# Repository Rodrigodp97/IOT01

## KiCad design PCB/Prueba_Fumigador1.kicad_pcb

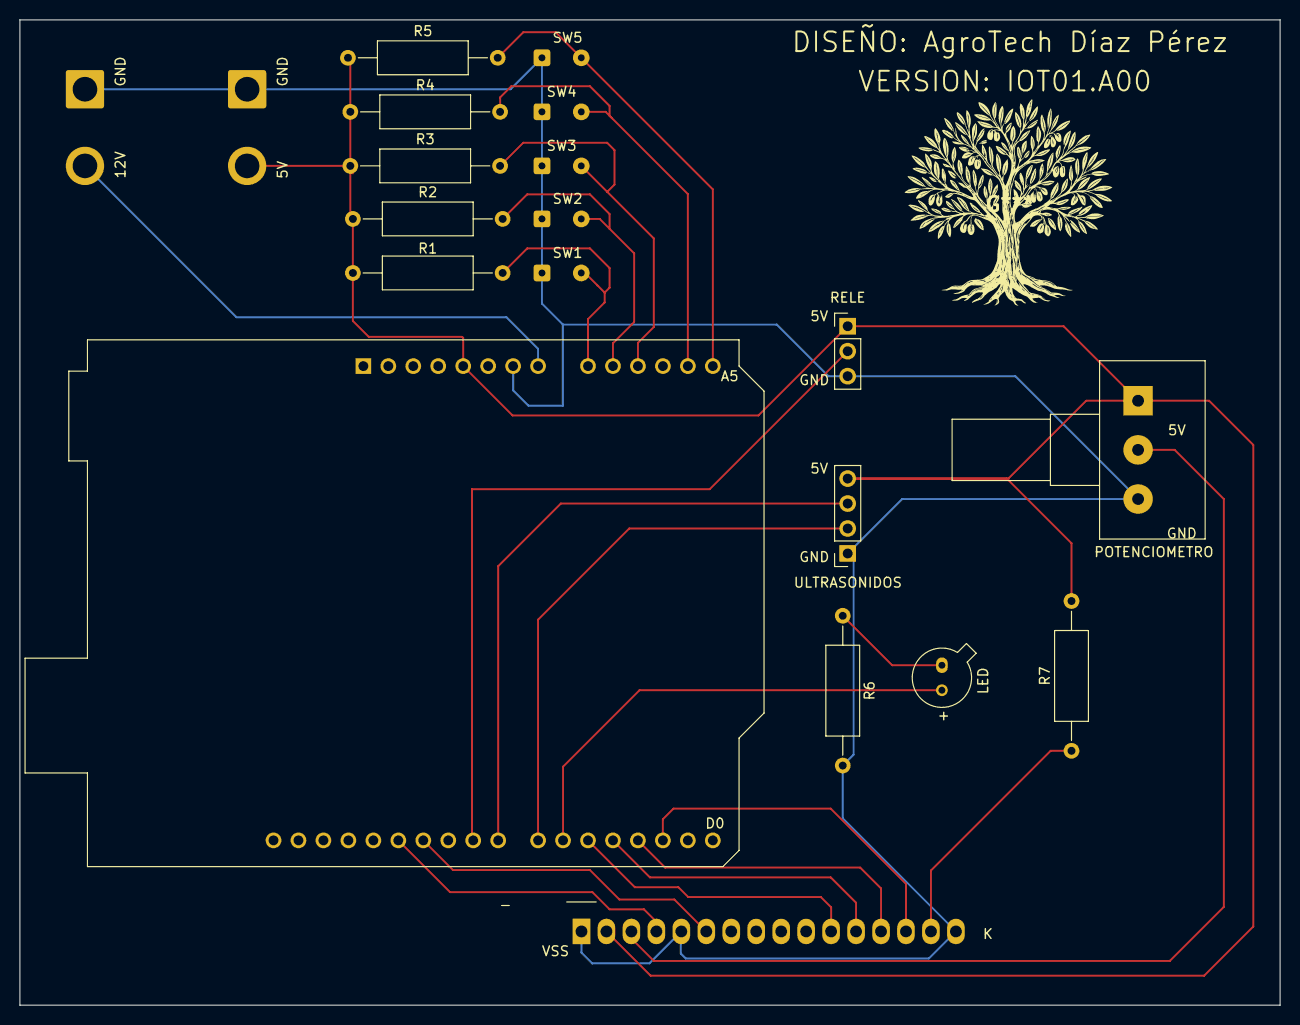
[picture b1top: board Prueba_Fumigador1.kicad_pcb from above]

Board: 2 copper layers, 128.2 x 100.2 mm, 20 parts (0 on the bottom side), 21 nets.

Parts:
12V: Conn_01x02; SolderWire-2sqmm_1x02_P7.8mm_D2mm_OD3.9mm
A5: Arduino_UNO_R3
D1: SFH460; TO-18-2_Window
DS1: WC1602A
GND: Conn_01x02; SolderWire-2sqmm_1x02_P7.8mm_D2mm_OD3.9mm
POTENCIOMETRO: R_Potentiometer; Potentiometer_Alps_RK163_Single_Horizontal
R1, R2, R3, R4, R5: 5k; R_Axial_DIN0309_L9.0mm_D3.2mm_P15.24mm_Horizontal
R6, R7: 200; R_Axial_DIN0309_L9.0mm_D3.2mm_P15.24mm_Horizontal
RELE: Conn_01x03_Pin; PinHeader_1x03_P2.54mm_Vertical
SW1: BOTON ARRIBA; SolderWire-0.15sqmm_1x02_P4mm_D0.5mm_OD1.5mm
SW2: BOTON ABAJO; SolderWire-0.15sqmm_1x02_P4mm_D0.5mm_OD1.5mm
SW3: BOTON OK; SolderWire-0.15sqmm_1x02_P4mm_D0.5mm_OD1.5mm
SW4: BOTON ESC; SolderWire-0.15sqmm_1x02_P4mm_D0.5mm_OD1.5mm
SW5: BOTON MANUAL; SolderWire-0.15sqmm_1x02_P4mm_D0.5mm_OD1.5mm
ULTRASONIDOS: Conn_01x04_Socket; PinSocket_1x04_P2.54mm_Vertical

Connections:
+5V: A5.5 (+5V), DS1.2 (VDD), GND.2, POTENCIOMETRO.1, R1.1, R2.1, R3.1, R4.1, R5.1, R7.2, RELE.1, ULTRASONIDOS.4
+12V: 12V.2, A5.8 (VIN)
A0: A5.9 (A0), R1.2, SW1.2
A1: A5.10 (A1), R2.2, SW2.2
A2: A5.11 (A2), R3.2, SW3.2
A4: A5.13 (SDA/A4), R4.2, SW4.2
A5: A5.14 (SCL/A5), R5.2, SW5.2
D2: A5.17 (D2), DS1.14 (D7)
D3: A5.18 (D3), DS1.13 (D6)
D4: A5.19 (D4), DS1.12 (D5)
D5: A5.20 (D5), DS1.11 (D4)
D6: A5.21 (D6), D1.2 (A)
D7: A5.22 (D7), ULTRASONIDOS.2
D8: A5.23 (D8), ULTRASONIDOS.3
D9: A5.24 (D9), RELE.2
D11: A5.26 (D11), DS1.6 (E)
D12: A5.27 (D12), DS1.4 (RS)
GND: 12V.1, A5.7 (GND), DS1.1 (VSS), DS1.5 (R/W), DS1.16 (LED(-)), GND.1, POTENCIOMETRO.3, R6.2, RELE.3, SW1.1, SW2.1, SW3.1, SW4.1, SW5.1, ULTRASONIDOS.1
unnamed: D1.1 (K), R6.1
unnamed: DS1.15 (LED(+)), R7.1
RPOT: DS1.3 (VO), POTENCIOMETRO.2

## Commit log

2025-05-23 Logo tractor
2025-07-09 Proyecto KiCad de la PCB
2026-01-15 Script de python con inferaz grafica con camara y configuraciones
2026-01-15 FW A00
2026-01-15 Se actualiza el codigo para poder controlarse desde la interfaz grafica y se desactivan todos los botones
2026-01-15 Primera prueba raspberry pi
2026-01-15 Prueba raspberry pi exitosa
2026-01-16 Se añaden los archivos de la version A00
2026-01-16 Se añaden modificaciones en la version beta A01 del arduino y se incluye la interfaz gráfica para que corra en raspberry pi
2026-02-18 Mejoras con la inclusion de mapas
2026-02-18 Actualizacion codigo arduino
2026-02-19 Actualizar app.py para mostrar mejor la camara
2026-02-19 Actualizar page1 con redimensionado camara
2026-02-28 Pruebas envio ubicacion a traves de conexion WiFi
2026-02-28 Actualizacion pantalla principal
2026-02-28 Comunicacion exitosa en envio ubicacion entre movil y raspberry
2026-03-03 Obtencion y representacion en mapas de la ubicacion GPS del movil
